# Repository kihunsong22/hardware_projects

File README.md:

View this project on [CADLAB.io](https://cadlab.io/project/1469). 

# hardware-projects
hardware designs and codes - some open-source, some from me

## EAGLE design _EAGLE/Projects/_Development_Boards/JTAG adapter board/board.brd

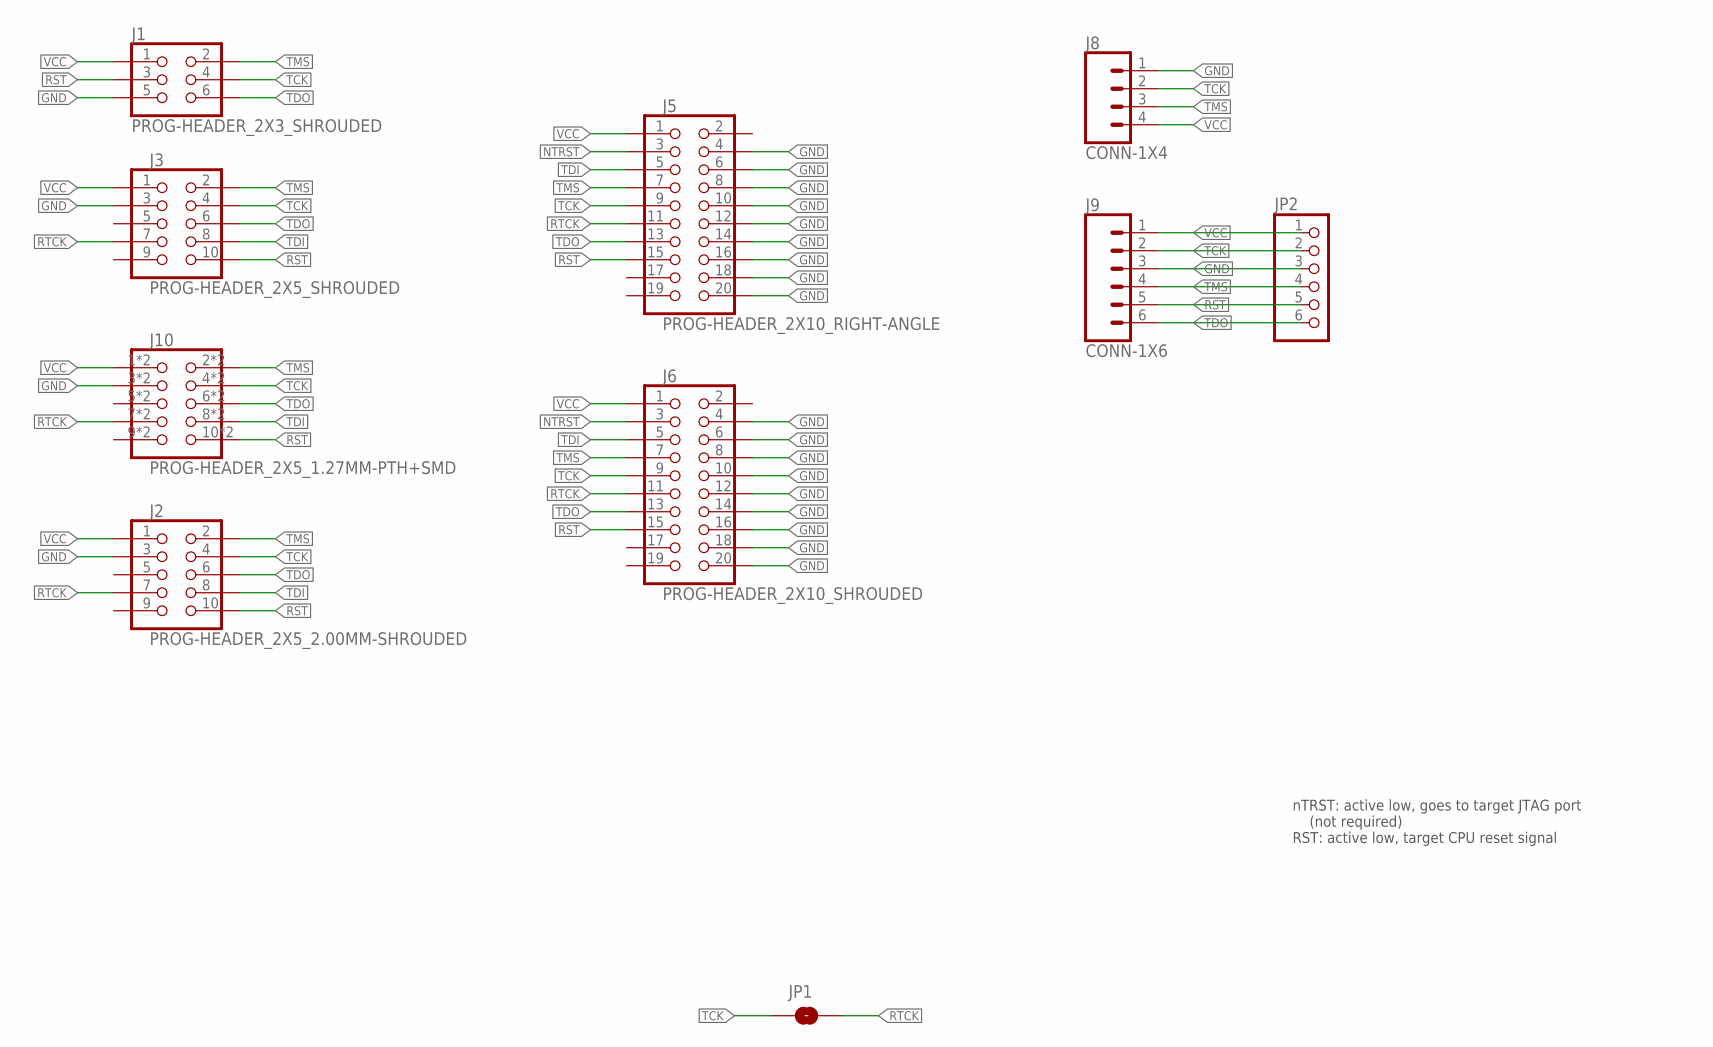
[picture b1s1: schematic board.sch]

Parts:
J1: PROG-HEADER_2X3_SHROUDED; 2X3-2.54MM-SHROUDED
J2: PROG-HEADER_2X5_2.00MM-SHROUDED; 2X5-2.00MM-SHROUDED
J3: PROG-HEADER_2X5_SHROUDED; 2X5-2.54MM-SHROUDED
J5: PROG-HEADER_2X10_RIGHT-ANGLE; 2X10-2.54MM-RIGHT-ANGLE
J6: PROG-HEADER_2X10_SHROUDED; 2X10-2.54MM-SHROUDED
J8: CONN-1X4; MOLEX-1X4-2.54MM
J9: CONN-1X6; MOLEX-1X6-2.54MM
J10: PROG-HEADER_2X5_1.27MM-PTH+SMD; 2X5-1.27MM_PTH+SMD
JP1: TCK-RTCK; SMT-JUMPER_2_NO_SILK
JP2: PINHD-1X6/OCT; 1X06/OCT

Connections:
2: J5.2, J6.2
GND: J1.5, J2.3, J3.3, J5.4, J5.6, J5.8, J5.10, J5.12, J5.14, J5.16, J5.18, J5.20, J6.4, J6.6, J6.8, J6.10, J6.12, J6.14, J6.16, J6.18, J6.20, J8.1, J9.3, J10.3, J10.13 (3), JP2.3
NTRST: J5.3, J6.3
RST: J1.3, J2.10, J3.10, J5.15, J6.15, J9.5, J10.10, J10.20 (10), JP2.5
RTCK: J2.7, J3.7, J5.11, J6.11, J10.7, J10.17 (7), JP1.2
TCK: J1.4, J2.4, J3.4, J5.9, J6.9, J8.2, J9.2, J10.4, J10.14 (4), JP1.1, JP2.2
TDI: J2.8, J3.8, J5.5, J6.5, J10.8, J10.18 (8)
TDO: J1.6, J2.6, J3.6, J5.13, J6.13, J9.6, J10.6, J10.16 (6), JP2.6
TMS: J1.2, J2.2, J3.2, J5.7, J6.7, J8.3, J9.4, J10.2, J10.12 (2), JP2.4
VCC: J1.1, J2.1, J3.1, J5.1, J6.1, J8.4, J9.1, J10.1, J10.11 (1), JP2.1

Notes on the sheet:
nTRST: active low, goes to target JTAG port (not required) RST: active low, target CPU reset signal

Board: 2 copper layers, 10 parts (1 on the bottom side), 10 nets, no tracks yet.

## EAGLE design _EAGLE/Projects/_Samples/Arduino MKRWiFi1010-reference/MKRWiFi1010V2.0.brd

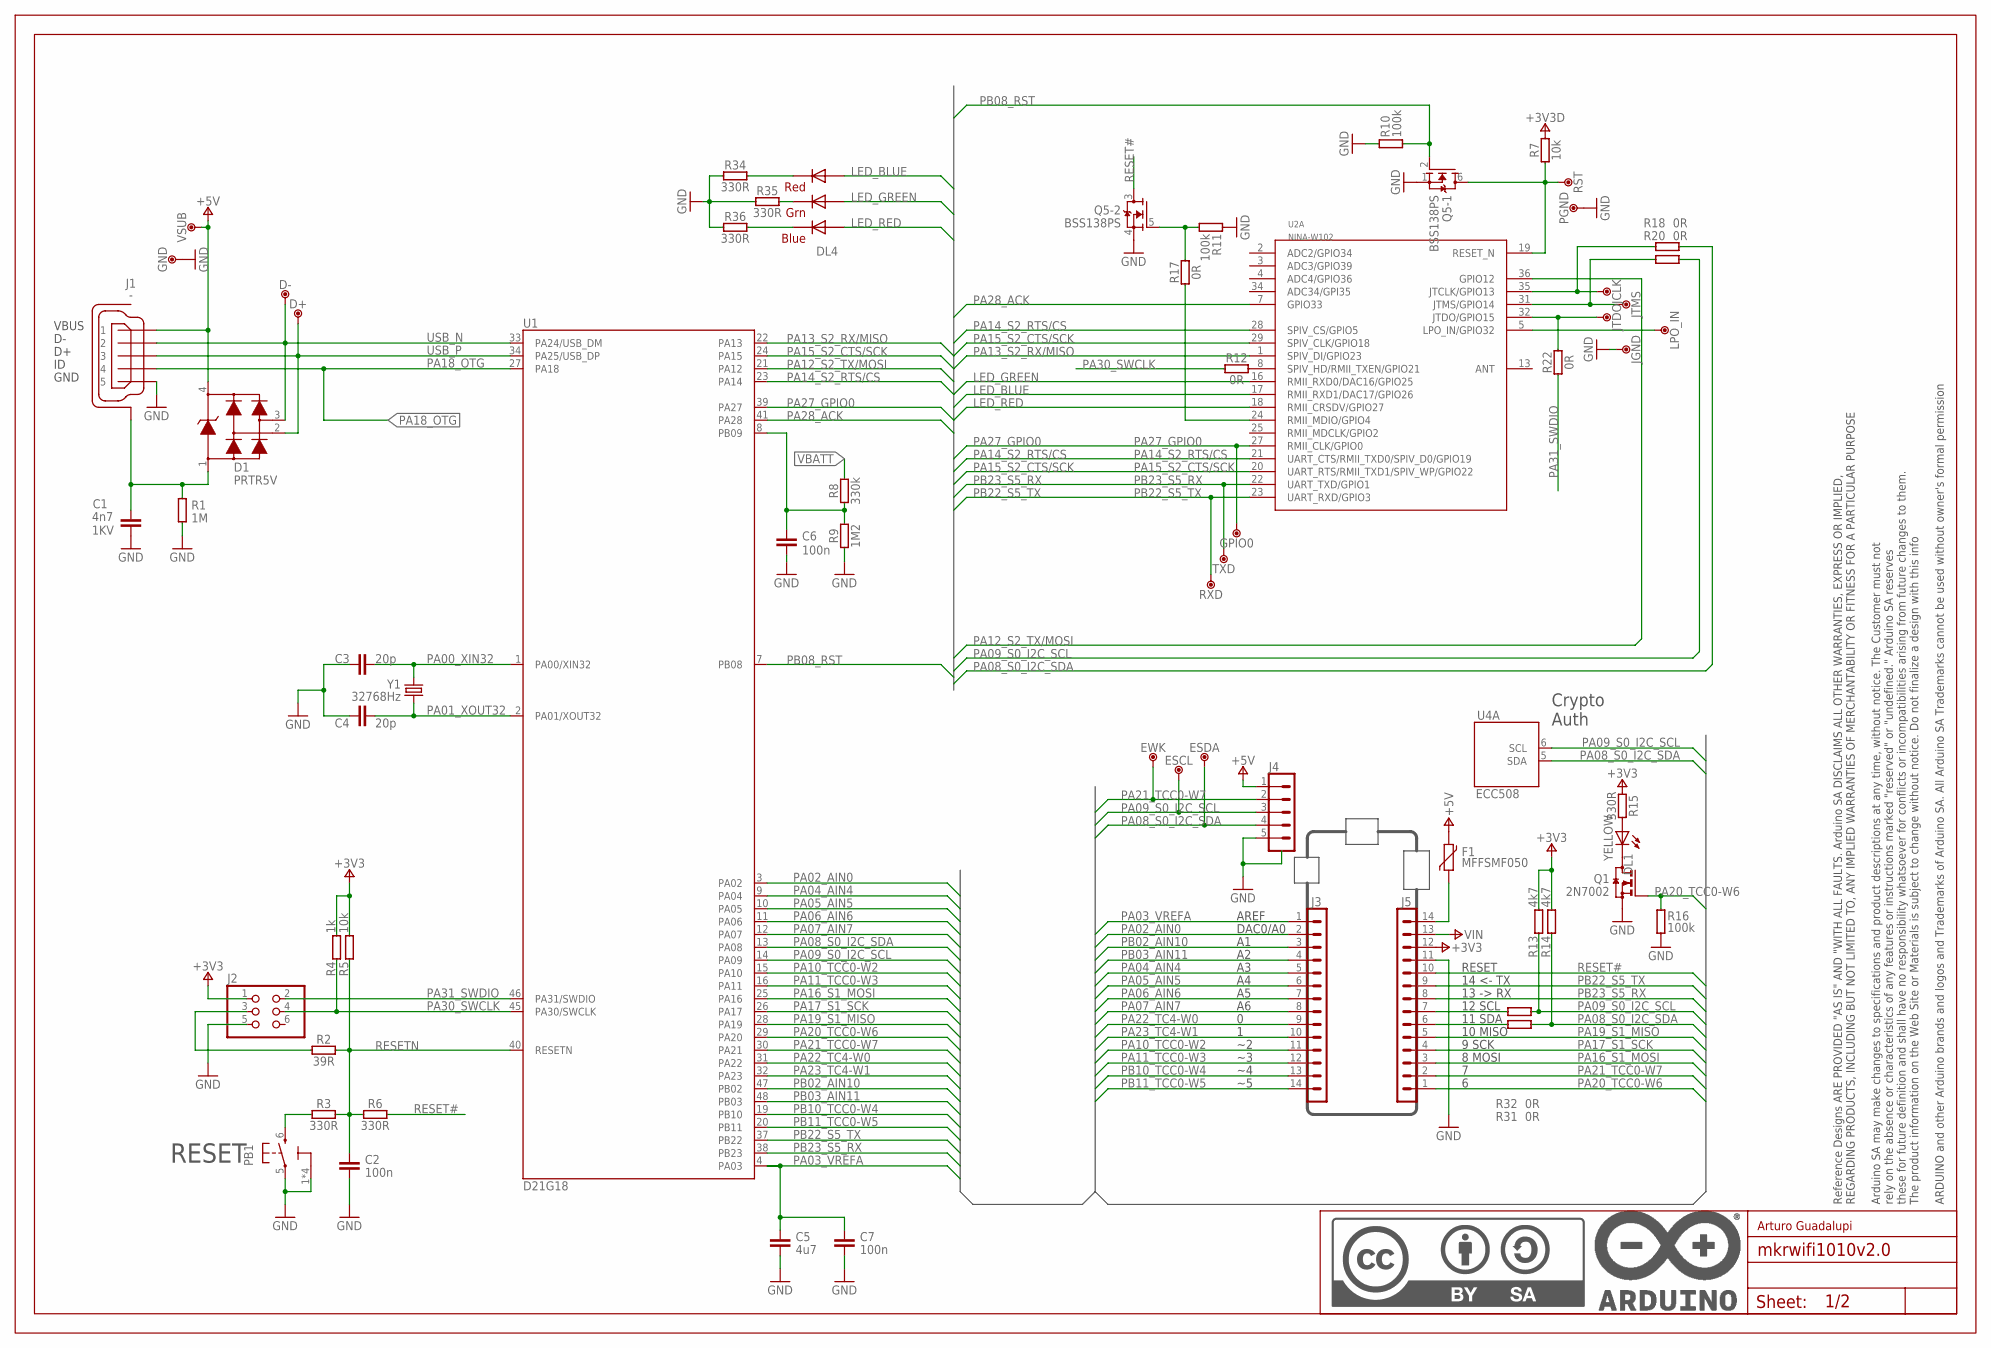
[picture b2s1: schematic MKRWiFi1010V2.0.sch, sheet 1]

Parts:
C1: 4n7; 0805-R2013X50N; VOLTAGE 1KV
C2, C6, C7: 100n; 0402-1005X55N
C3, C4: 20p; 0402-1005X55N
C5: 4u7; 0402-1005X55N
D1: PRTR5V; SOT190P230X110-4N
D+: DNP; TP-1.00MM
D-: DNP; TP-1.00MM
DL1: YELLOW; LEDC1608X80N-AK
DL4: RGB; RGBLED
ESCL: DNP; TP-1.00MM
ESDA: DNP; TP-1.00MM
EWK: DNP; TP-1.00MM
F1: MFFSMF050; 0603-1608X90N
FRAME1: DNP; FRAME
GND: DNP; TP-1.00MM
GPIO0: DNP; TP-0.8MM
J1: -; ZX62-AB-5PA
J2: DNP; 2X3_SMT
J3, J5: -; 1X14_SMD_TH
J4: -; SM05B-SRSS-TB
JCLK: DNP; TP-0.8MM
JGND: DNP; TP-0.8MM
JTDO: DNP; TP-0.8MM
JTMS: DNP; TP-0.8MM
LPO_IN: DNP; TP-1.27MM
PB1: PTS820; C&K_PTS820_NO_HOLES
PGND: DNP; TP-0.8MM
Q1: 2N7002; SOTFL50P160X78-3
Q5: BSS138PS; SOT363
R1: 1M; 0402-1005X55N
R2: 39R; 0402-1005X55N
R3, R6, R15, R34, R35, R36: 330R; 0402-1005X55N
R4: 1k; 0402-1005X55N
R5, R7: 10k; 0402-1005X55N
R8: 330k; 0402-1005X55N
R9: 1M2; 0402-1005X55N
R10, R11, R16: 100k; 0402-1005X55N
R12, R17, R18, R20, R22, R31, R32: 0R; 0402-1005X55N
R13, R14: 4k7; 0402-1005X55N
RST: DNP; TP-0.8MM
RXD: DNP; TP-0.8MM
TXD: DNP; TP-0.8MM
U1: D21G18; QFN50P700X700X90-49XN-EPSQ515
U2: NINA-W102; NINA-W1X
U4: ECC508; SON50P300X200X60-9N-EP160X140
VSUB: DNP; TP-1.00MM
Y1: 32768Hz; ABS07

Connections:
+3V3: J2.1, J5.12, R4.2, R5.2, R13.2, R14.2, R15.1; also elsewhere on the board
+3V3D: R7.2; also elsewhere on the board
+5V: D1.4, F1.2, J1.1, J4.1, VSUB.X; also elsewhere on the board
GND: C1.2, C2.2, C3.1, C4.1, C5.2, C6.2, C7.2, GND.X, J1.5, J2.5, J4.5, J4.SH1 (SH), J4.SH2 (SH), J5.11, JGND.X, PB1.1 (3), PB1.2 (3), PB1.3, PB1.4 (3), PB1.5 (1), PGND.X, Q1.S, Q5.1 (S), Q5.4 (S), R1.1, R9.1, R10.2, R11.2, R16.1, R34.1, R35.1, R36.1; also elsewhere on the board
LED_BLUE: DL4.2 (RED_A), U2.17 (RMII_RXD1/DAC17/GPIO26)
LED_GREEN: DL4.1 (GREEN_A), U2.16 (RMII_RXD0/DAC16/GPIO25)
LED_RED: DL4.3 (BLUE_A), U2.18 (RMII_CRSDV/GPIO27)
N17658775: PB1.6 (2), R3.1
unnamed: C1.1, D1.1, J1.6 (SH), J1.7 (SH), J1.8 (SH), J1.9 (SH), J1.10 (SH), J1.11 (SH), R1.2
unnamed: F1.1, J5.14
unnamed: J2.3, R2.1
unnamed: J5.7, R32.1
unnamed: C6.1, R8.1, R9.2, U1.8 (PB09)
unnamed: DL1.A, R15.2
unnamed: J5.6, R31.1
unnamed: Q5.6 (D), R7.1, RST.X, U2.19 (RESET_N)
unnamed: DL1.C, Q1.D
unnamed: JCLK.X, R18.1, U2.35 (JTCLK/GPIO13)
unnamed: JTMS.X, R20.1, U2.31 (JTMS/GPIO14)
unnamed: R17.1, U2.24 (RMII_MDIO/GPIO4)
unnamed: DL4.5 (RED_C), R34.2
unnamed: DL4.6 (GREEN_C), R35.2
unnamed: DL4.4 (BLUE_C), R36.2
unnamed: LPO_IN.X, U2.5 (LPO_IN/GPIO32)
unnamed: JTDO.X, R22.2, U2.32 (JTDO/GPIO15)
unnamed: R12.2, U2.8 (SPIV_HD/RMII_TXEN/GPIO21)
unnamed: Q5.5 (G), R11.1, R17.2
PA00_XIN32: C3.2, U1.1 (PA00/XIN32), Y1.2
PA01_XOUT32: C4.2, U1.2 (PA01/XOUT32), Y1.1
PA02_AIN0: J3.2, U1.3 (PA02)
PA03_VREFA: C5.1, C7.1, J3.1, U1.4 (PA03)
PA04_AIN4: J3.5, U1.9 (PA04)
PA05_AIN5: J3.6, U1.10 (PA05)
PA06_AIN6: J3.7, U1.11 (PA06)
PA07_AIN7: J3.8, U1.12 (PA07)
PA08_S0_I2C_SDA: ESDA.X, J4.4, R14.1, R18.2, R31.2, U1.13 (PA08), U4.5 (SDA); also elsewhere on the board
PA09_S0_I2C_SCL: ESCL.X, J4.3, R13.1, R20.2, R32.2, U1.14 (PA09), U4.6 (SCL); also elsewhere on the board
PA10_TCC0-W2: J3.11, U1.15 (PA10)
PA11_TCC0-W3: J3.12, U1.16 (PA11)
PA12_S2_TX/MOSI: U1.21 (PA12), U2.36 (GPIO12)
PA13_S2_RX/MISO: U1.22 (PA13), U2.1 (SPIV_DI/GPIO23)
PA14_S2_RTS/CS: U1.23 (PA14), U2.21 (UART_CTS/RMII_TXD0/SPIV_D0/GPIO19), U2.28 (SPIV_CS/GPIO5)
PA15_S2_CTS/SCK: U1.24 (PA15), U2.20 (UART_RTS/RMII_TXD1/SPIV_WP/GPIO22), U2.29 (SPIV_CLK/GPIO18)
PA16_S1_MOSI: J5.3, U1.25 (PA16)
PA17_S1_SCK: J5.4, U1.26 (PA17)
PA18_OTG: J1.4, U1.27 (PA18); also elsewhere on the board
PA19_S1_MISO: J5.5, U1.28 (PA19)
PA20_TCC0-W6: J5.1, Q1.G, R16.2, U1.29 (PA20)
PA21_TCC0-W7: EWK.X, J4.2, J5.2, U1.30 (PA21)
PA22_TC4-W0: J3.9, U1.31 (PA22)
PA23_TC4-W1: J3.10, U1.32 (PA23)
PA27_GPIO0: GPIO0.X, U1.39 (PA27), U2.27 (RMII_CLK/GPIO0)
PA28_ACK: U1.41 (PA28), U2.7 (GPIO33)
PA30_SWCLK: J2.4, R4.1, R12.1, U1.45 (PA30/SWCLK)
PA31_SWDIO: J2.2, R22.1, U1.46 (PA31/SWDIO)
PB02_AIN10: J3.3, U1.47 (PB02)
PB03_AIN11: J3.4, U1.48 (PB03)
PB08_RST: Q5.2 (G), R10.1, U1.7 (PB08)
PB10_TCC0-W4: J3.13, U1.19 (PB10)
PB11_TCC0-W5: J3.14, U1.20 (PB11)
PB22_S5_TX: J5.9, RXD.X, U1.37 (PB22), U2.23 (UART_RXD/GPIO3)
PB23_S5_RX: J5.8, TXD.X, U1.38 (PB23), U2.22 (UART_TXD/GPIO1)
RESET#: J5.10, Q5.3 (D), R6.2
RESETN: C2.1, R2.2, R3.2, R5.1, R6.1, U1.40 (RESETN)
USB_N: D1.3, D-.X, J1.2, U1.33 (PA24/USB_DM)
USB_P: D1.2, D+.X, J1.3, U1.34 (PA25/USB_DP)
VBATT: R8.2; also elsewhere on the board
VIN: J5.13; also elsewhere on the board

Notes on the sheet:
14 <- TX
13 -> RX
12 SCL
RESET
11 SDA
8 MOSI
9 SCK
10 MISO
AREF
DAC0/A0
Crypto Auth
Arturo Guadalupi

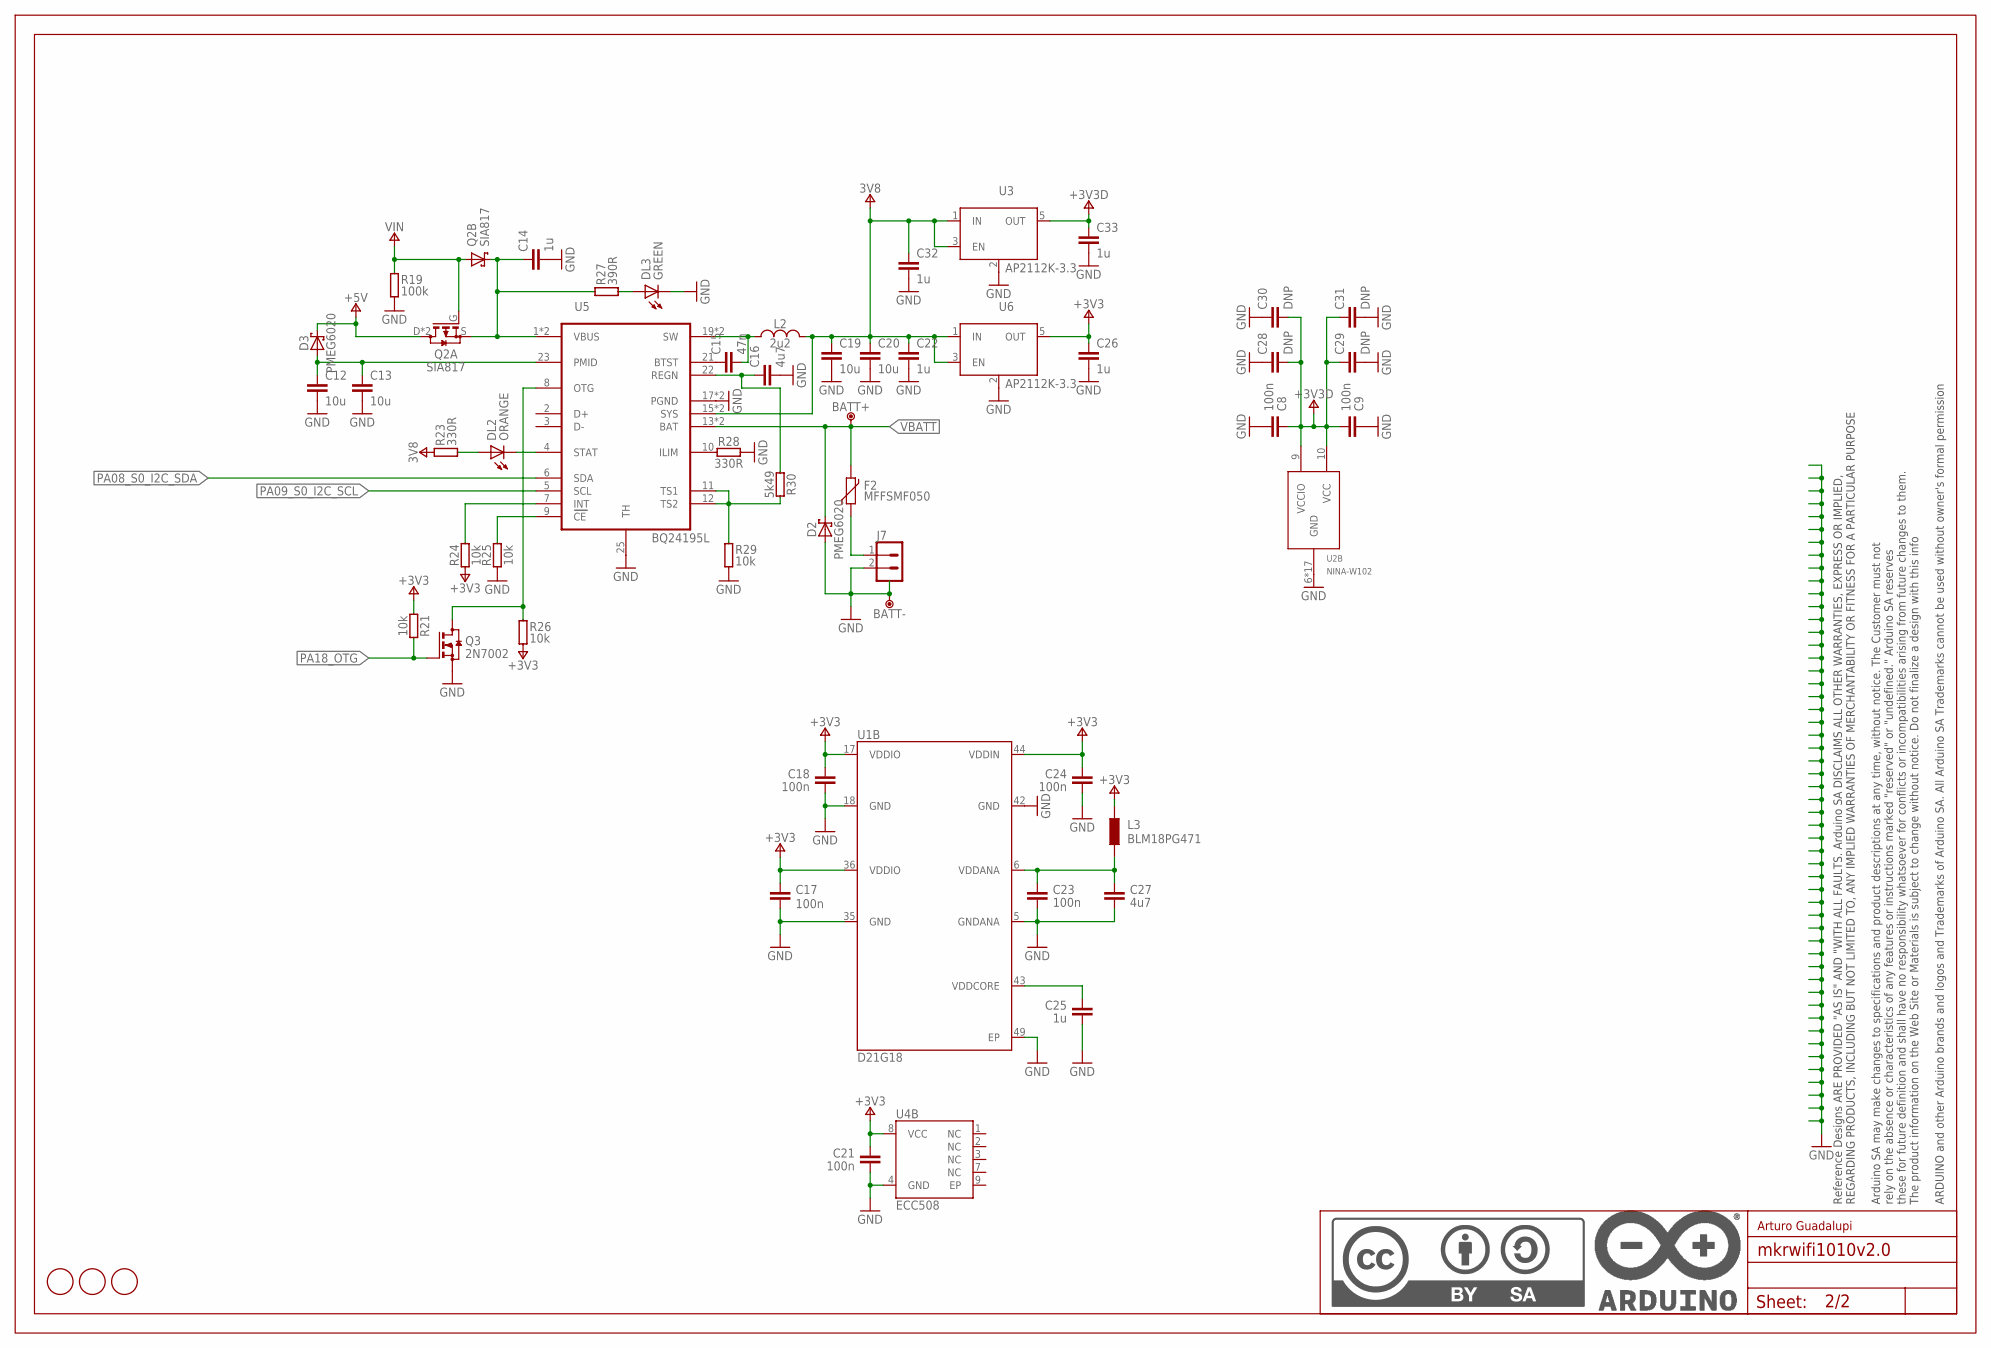
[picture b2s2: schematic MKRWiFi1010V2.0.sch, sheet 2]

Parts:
BATT+: DNP; TP-1.00MM
BATT-: DNP; TP-1.00MM
C8, C9, C17, C18, C21, C23, C24: 100n; 0402-1005X55N
C12, C13, C19, C20: 10u; 0603-1608X90N
C14, C22, C25, C26, C32, C33: 1u; 0402-1005X55N
C15: 47n; 0402-1005X55N
C16: 4u7; 0402-1005X55N
C27: 4u7; 0603-1608X90N
C28, C29: DNP; 0402-1005X55N
C30, C31: DNP; 0603-1608X90N
D2, D3: PMEG6020; SODFL3517X110N
DL2: ORANGE; LEDC1608X80N-AK
DL3: GREEN; LEDC1608X80N-AK
F2: MFFSMF050; 0603-1608X90N
FD1, FD2, FD3: DNP; FD-1-1.5
FRAME2: DNP; FRAME
J7: -; JST-S2B-PH-SM4-TB
L2: 2u2; SRP4020
L3: BLM18PG471; 0603-1608X90N
Q2: SIA817; SON65P205X205X75-8N-MWSD
Q3: 2N7002; SOTFL50P160X78-3
R19: 100k; 0402-1005X55N
R21, R24, R25, R26, R29: 10k; 0402-1005X55N
R23, R28: 330R; 0402-1005X55N
R27: 390R; 0402-1005X55N
R30: 5k49; 0402-1005X55N
U1: D21G18; QFN50P700X700X90-49XN-EPSQ515
U2: NINA-W102; NINA-W1X
U3, U6: AP2112K-3.3; SOT25
U4: ECC508; SON50P300X200X60-9N-EP160X140
U5: BQ24195L; QFN24

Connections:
+3V3: C17.1, C18.1, C21.1, C24.1, C26.1, L3.1, R21.1, R24.1, R26.1, U1.17 (VDDIO), U1.36 (VDDIO), U1.44 (VDDIN), U4.8 (VCC), U6.5 (OUT); also elsewhere on the board
+3V3D: C8.1, C9.2, C28.2, C29.1, C30.2, C31.1, C33.1, U2.9 (VCCIO), U2.10 (VCC), U3.5 (OUT); also elsewhere on the board
+3V8: C19.1, C20.1, C22.1, C32.1, L2.2, R23.2, U3.1 (IN), U3.3 (EN), U5.15 (SYS), U5.16 (SYS), U6.1 (IN), U6.3 (EN)
+5V: D3.C, Q2.D, Q2.D2 (D); also elsewhere on the board
GND: BATT-.X, C8.2, C9.1, C12.2, C13.2, C14.2, C16.2, C17.2, C18.2, C19.2, C20.2, C21.2, C22.2, C23.2, C24.2, C25.2, C26.2, C27.2, C28.1, C29.2, C30.1, C31.2, C32.2, C33.2, D2.A, DL3.C, J7.2, J7.3 (SH), J7.4 (SH), Q3.S, R19.1, R25.1, R28.2, R29.1, U1.5 (GNDANA), U1.18 (GND), U1.35 (GND), U1.42 (GND), U1.49 (EP), U2.6 (GND), U2.12 (GND), U2.14 (GND), U2.26 (GND), U2.30 (GND), U2.GND@1 (GND), U2.GND@2 (GND), U2.GND@3 (GND), U2.GND@4 (GND), U2.GND@5 (GND), U2.GND@6 (GND), U2.GND@7 (GND), U2.GND@8 (GND), U2.GND@9 (GND), U2.GND@10 (GND), U2.GND@11 (GND), U2.GND@12 (GND), U3.2 (GND/ADJ), U4.4 (GND), U5.17 (PGND), U5.18 (PGND), U5.25 (TH), U6.2 (GND/ADJ); also elsewhere on the board
N17798864: DL2.A, R23.1
N17834267: DL3.A, R27.1
N17852357: C23.1, C27.1, L3.2, U1.6 (VDDANA)
N17852431: C25.1, U1.43 (VDDCORE)
unnamed: F2.1, J7.1
unnamed: C15.2, L2.1, U5.19 (SW), U5.20 (SW)
unnamed: C14.1, Q2.K (C), Q2.K2 (C), Q2.S, R27.2, U5.1 (VBUS), U5.24 (VBUS)
unnamed: C15.1, U5.21 (BTST)
unnamed: R28.1, U5.10 (ILIM)
unnamed: C16.1, R30.1, U5.22 (REGN)
unnamed: Q3.D, R26.2, U5.8 (OTG)
unnamed: R29.2, R30.2, U5.11 (TS1), U5.12 (TS2)
unnamed: R25.2, U5.9 (CE)
PA08_S0_I2C_SDA: U5.6 (SDA); also elsewhere on the board
PA09_S0_I2C_SCL: U5.5 (SCL); also elsewhere on the board
PA18_OTG: Q3.G, R21.2; also elsewhere on the board
PMICINT: R24.2, U5.7 (INT)
STAT: DL2.C, U5.4 (STAT)
VBATT: BATT+.X, D2.C, F2.2, U5.13 (BAT), U5.14 (BAT); also elsewhere on the board
VIN: Q2.A, Q2.G, R19.2; also elsewhere on the board
VUSB1: C12.1, C13.1, D3.A, U5.23 (PMID)

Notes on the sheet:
Arturo Guadalupi

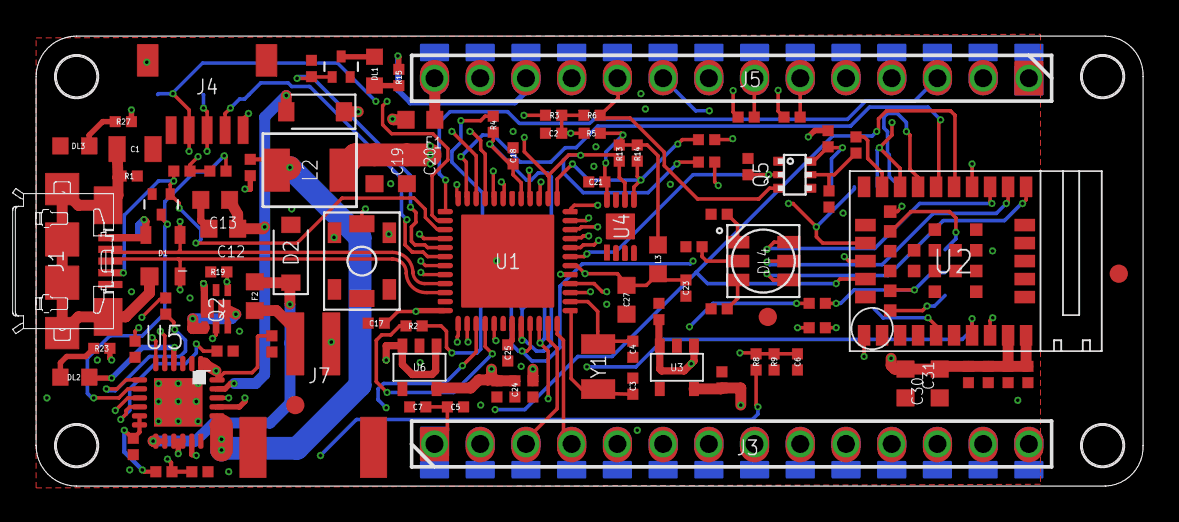
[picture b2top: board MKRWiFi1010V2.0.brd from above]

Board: 4 copper layers, 61.5 x 25.0 mm, 123 parts (1 on the bottom side), 85 nets.

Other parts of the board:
U$5, U$6, U$7, U$8: MH_RND_F_2.2MM_NM

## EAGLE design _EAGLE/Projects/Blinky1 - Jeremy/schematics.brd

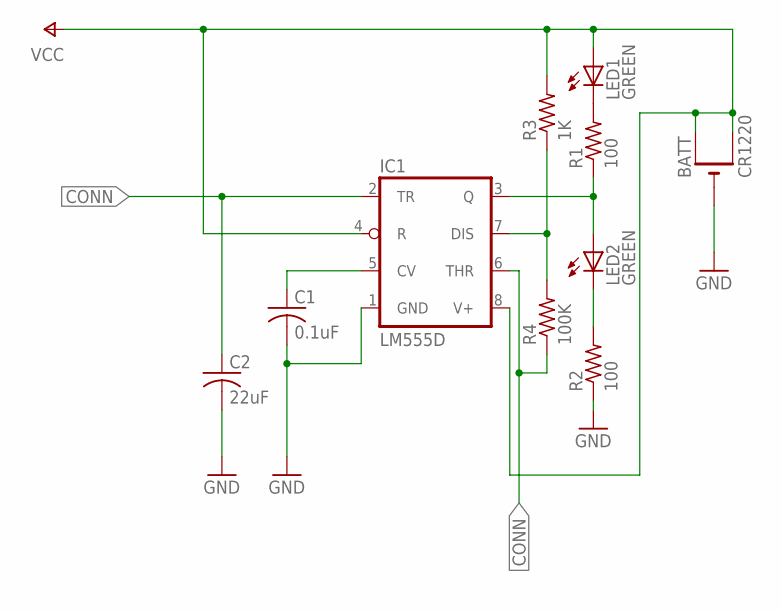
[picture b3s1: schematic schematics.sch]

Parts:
BATT: CR1220; CR1220-SMD
C1: 0.1uF; C0805
C2: 22uF; C0805
IC1: LM555D; SO08
LED1, LED2: GREEN; CHIPLED_0805
R1, R2: 100; R0805
R3: 1K; R0805
R4: 100K; R0805

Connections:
CONN: C2.1, IC1.2 (TR), IC1.6 (THR), R4.1
GND: BATT.-, C1.2, C2.2, IC1.1 (GND), R2.1
unnamed: IC1.3 (Q), LED2.A, R1.1
unnamed: LED1.C, R1.2
unnamed: LED2.C, R2.2
unnamed: IC1.7 (DIS), R3.1, R4.2
unnamed: C1.1, IC1.5 (CV)
V+: BATT.+$1 (+), BATT.+$2 (+1), IC1.4 (R), IC1.8 (V+), LED1.A, R3.2

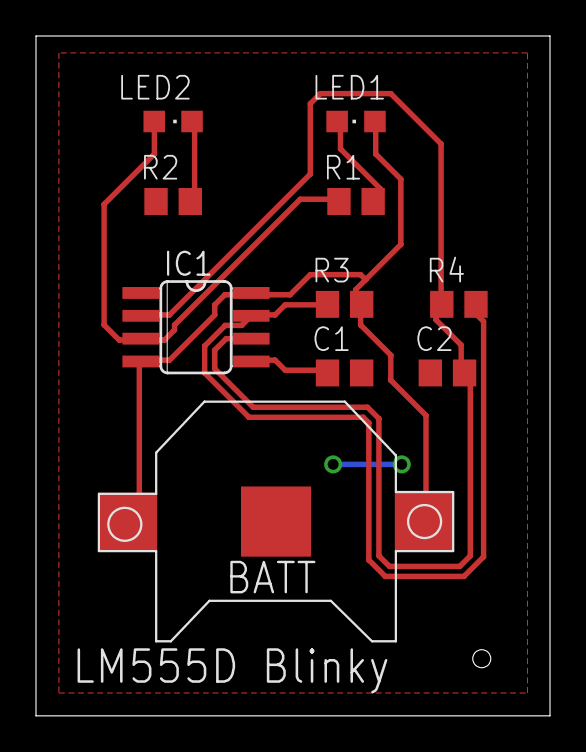
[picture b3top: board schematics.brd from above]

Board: 2 copper layers, 28.6 x 37.8 mm, 10 parts (0 on the bottom side), 8 nets.

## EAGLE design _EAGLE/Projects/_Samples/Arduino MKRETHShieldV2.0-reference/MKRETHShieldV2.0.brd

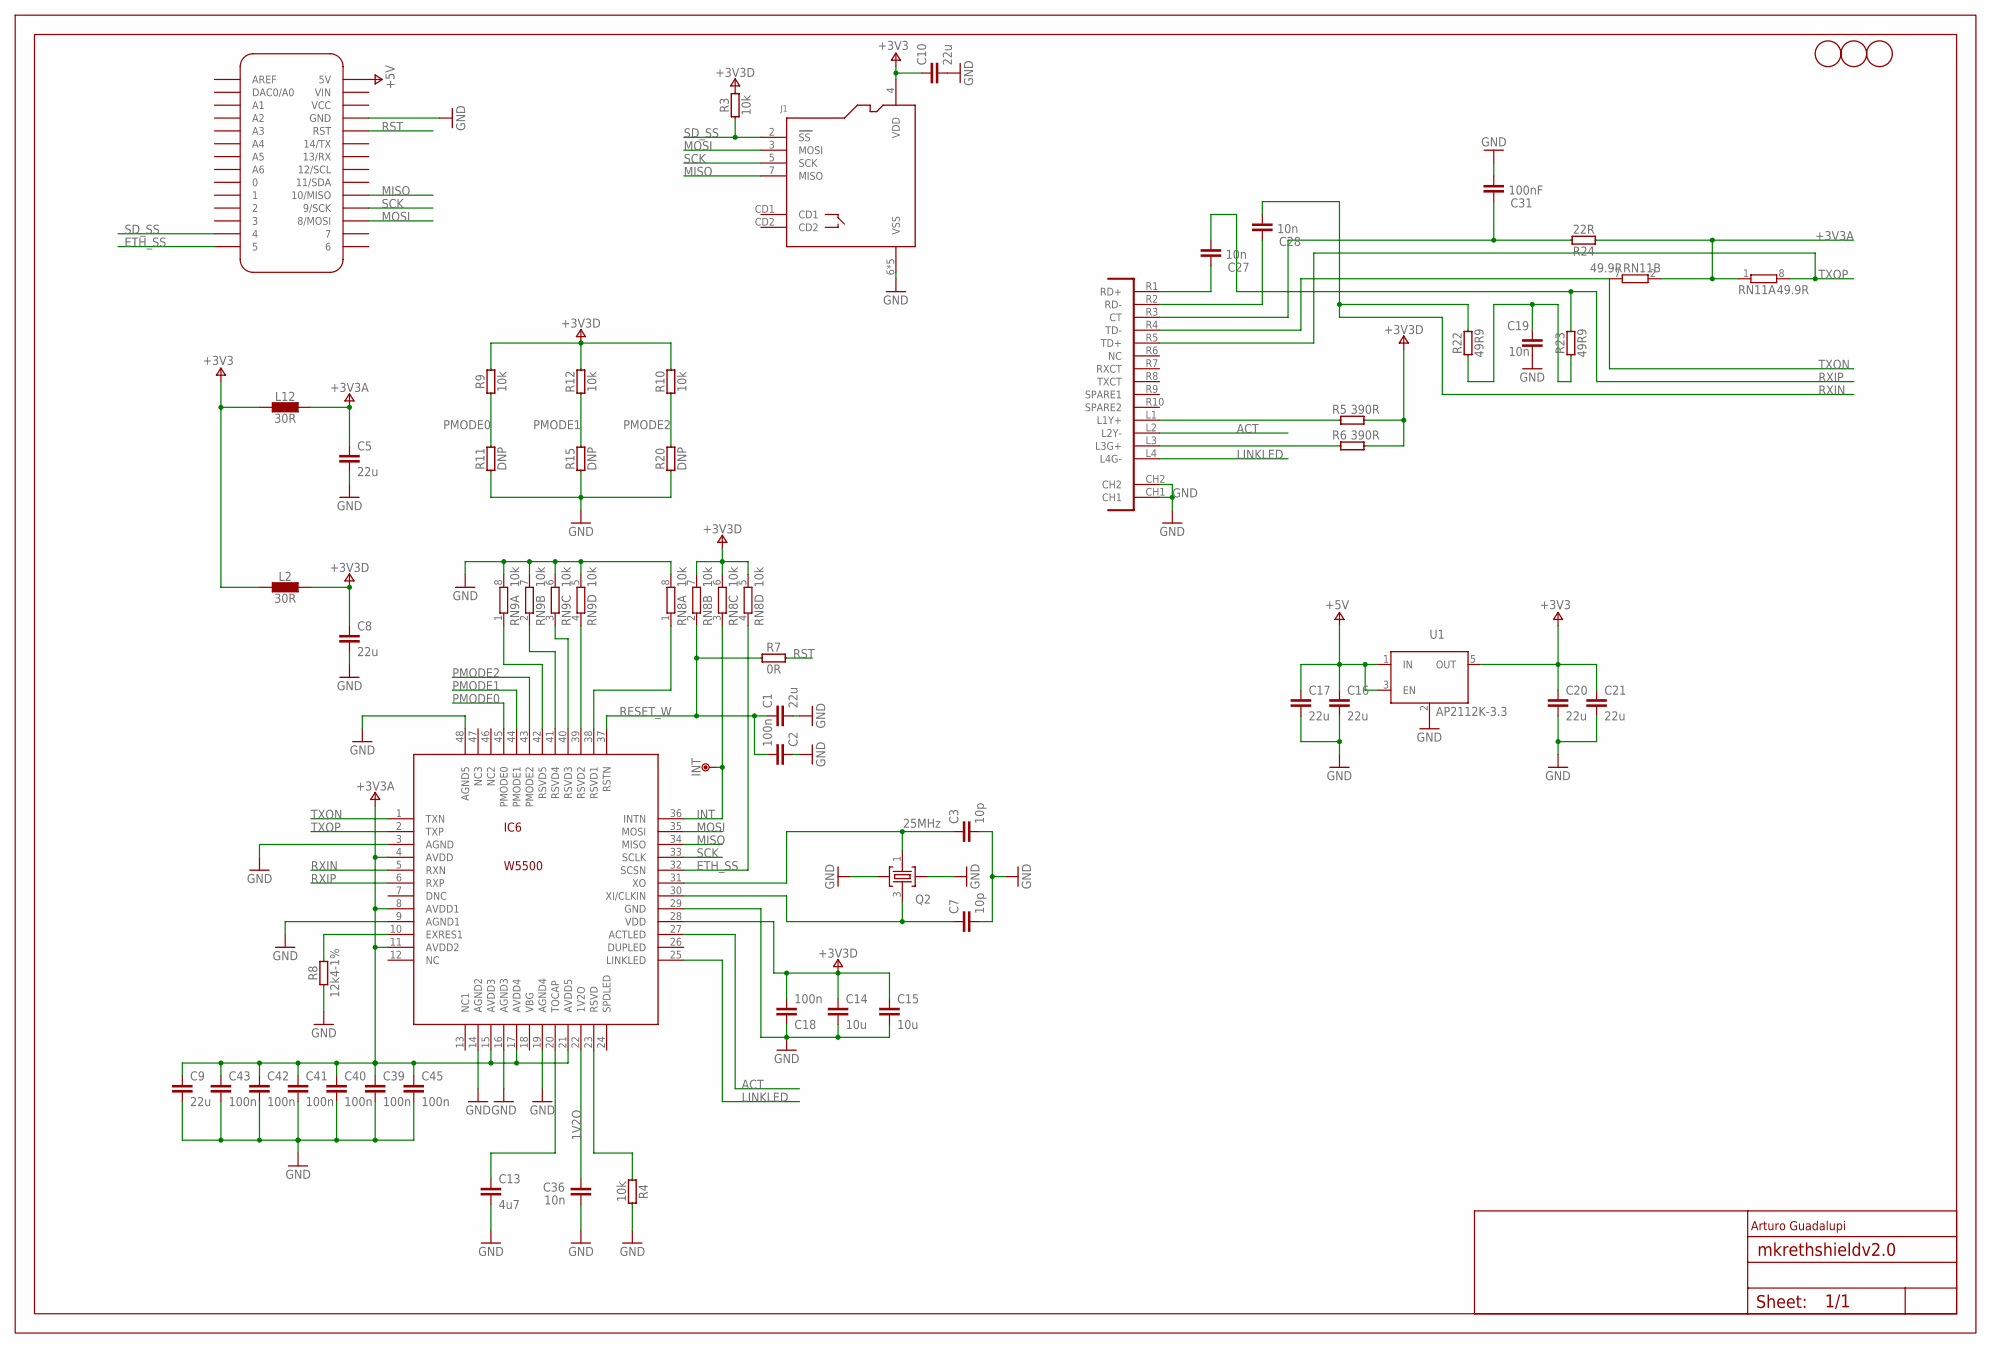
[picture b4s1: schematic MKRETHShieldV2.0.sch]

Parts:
C1, C5, C8, C9, C10, C16, C17, C20, C21: 22u; 0805-R2013X50N
C2, C18, C39, C40, C41, C42, C43, C45: 100n; 0402-1005X55N
C3, C7: 10p; 0402-1005X55N
C13: 4u7; 0603-1608X90N
C14, C15: 10u; 0603-1608X90N
C19, C27, C28, C36: 10n; 0402-1005X55N
C31: 100nF; 0402-1005X55N
FRAME1: DNP; FRAME
IC6: W5500; TQFP48-7X7
INT: DNP; TP-1.27MM
J1: -; AMPHENOL_114-00841-68
L2, L12: 30R; 0805-R2013X50N
MKR1: DNP; MKRBOARD-DIM
Q2: 25MHz; CRYSTAL3.2X2.5
R3, R4, R9, R10, R12: 10k; 0402-1005X55N
R5, R6: 390R; 0402-1005X55N
R7: 0R; 0402-1005X55N
R8: 12k4-1%; 0402-1005X55N
R11, R15, R20: DNP; 0402-1005X55N
R22, R23: 49R9; 0402-1005X55N
R24: 22R; 0402-1005X55N
RN8, RN9: 10k; CAY16
RN11: 49.9R; CAY16
U1: AP2112K-3.3; SOT25
U$1, U$2, U$3: DNP; FD-1-1.5
UC1: -; POE-RJ45

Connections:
1V2O: C36.2, IC6.22 (1V2O)
+3V3: C10.1, C20.1, C21.1, J1.4 (VDD), L2.1, L12.1, U1.5 (OUT)
+3V3A: C5.1, C9.1, C39.1, C40.1, C41.1, C42.1, C43.1, C45.1, IC6.4 (AVDD), IC6.8 (AVDD1), IC6.11 (AVDD2), IC6.15 (AVDD3), IC6.17 (AVDD4), IC6.21 (AVDD5), L12.2, R24.1, RN11.1, RN11.2 (1)
+3V3D: C8.1, C14.1, C15.1, C18.2, IC6.28 (VDD), L2.2, R3.2, R5.2, R6.2, R9.2, R10.2, R12.2, RN8.5 (2), RN8.6 (2), RN8.7 (2)
+5V: C16.1, C17.1, MKR1.5V, U1.1 (IN), U1.3 (EN)
ACT: IC6.27 (ACTLED), UC1.L2 (L2Y-)
DUPLED: IC6.26 (DUPLED)
ETH_SS: IC6.32 (SCSN), MKR1.5, RN8.4 (1)
GND: C1.2, C2.1, C3.2, C5.2, C7.2, C8.2, C9.2, C10.2, C13.2, C14.2, C15.2, C16.2, C17.2, C18.1, C19.1, C20.2, C21.2, C31.1, C36.1, C39.2, C40.2, C41.2, C42.2, C43.2, C45.2, IC6.3 (AGND), IC6.9 (AGND1), IC6.14 (AGND2), IC6.16 (AGND3), IC6.19 (AGND4), IC6.29 (GND), IC6.48 (AGND5), J1.6 (VSS), J1.SH1 (VSS), J1.SH2 (VSS), J1.SH3 (VSS), J1.SH4 (VSS), MKR1.GND, Q2.2, Q2.4, R4.1, R8.1, R11.1, R15.1, R20.1, RN8.8 (2), RN9.5 (2), RN9.6 (2), RN9.7 (2), RN9.8 (2), U1.2 (GND/ADJ), UC1.CH1, UC1.CH2
INT: IC6.36 (INTN), INT.X, RN8.3 (1)
LINKLED: IC6.25 (LINKLED), UC1.L4 (L4G-)
MISO: IC6.34 (MISO), J1.7 (MISO), MKR1.10 (10/MISO)
MOSI: IC6.35 (MOSI), J1.3 (MOSI), MKR1.8 (8/MOSI)
unnamed: C3.1, IC6.31 (XO), Q2.1
unnamed: IC6.39 (RSVD2), RN9.4 (1)
unnamed: R6.1, UC1.L3 (L3G+)
unnamed: IC6.23 (RSVD), R4.2
unnamed: R5.1, UC1.L1 (L1Y+)
unnamed: C19.2, R22.1, R23.1
unnamed: C27.2, UC1.R1 (RD+)
unnamed: C28.2, UC1.R2 (RD-)
unnamed: IC6.40 (RSVD3), RN9.3 (1)
unnamed: IC6.41 (RSVD4), RN9.2 (1)
unnamed: C31.2, R24.2, UC1.R3 (CT)
unnamed: IC6.42 (RSVD5), RN9.1
unnamed: C13.1, IC6.20 (TOCAP)
unnamed: IC6.38 (RSVD1), RN8.1
unnamed: IC6.10 (EXRES1), R8.2
NC: IC6.12 (NC)
OSC2E2: C7.1, IC6.30 (XI/CLKIN), Q2.3
PMODE0: IC6.45 (PMODE0), R9.1, R11.2
PMODE1: IC6.44 (PMODE1), R12.1, R15.2
PMODE2: IC6.43 (PMODE2), R10.1, R20.2
RESET_W: C1.1, C2.2, IC6.37 (RSTN), R7.1, RN8.2 (1)
RST: MKR1.RST, R7.2
RXIN: C28.1, IC6.5 (RXN), R22.2
RXIP: C27.1, IC6.6 (RXP), R23.2
SCK: IC6.33 (SCLK), J1.5 (SCK), MKR1.9 (9/SCK)
SD_SS: J1.2 (SS), MKR1.4, R3.1
TXON: IC6.1 (TXN), RN11.7 (2), UC1.R4 (TD-)
TXOP: IC6.2 (TXP), RN11.8 (2), UC1.R5 (TD+)

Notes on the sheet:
Arturo Guadalupi

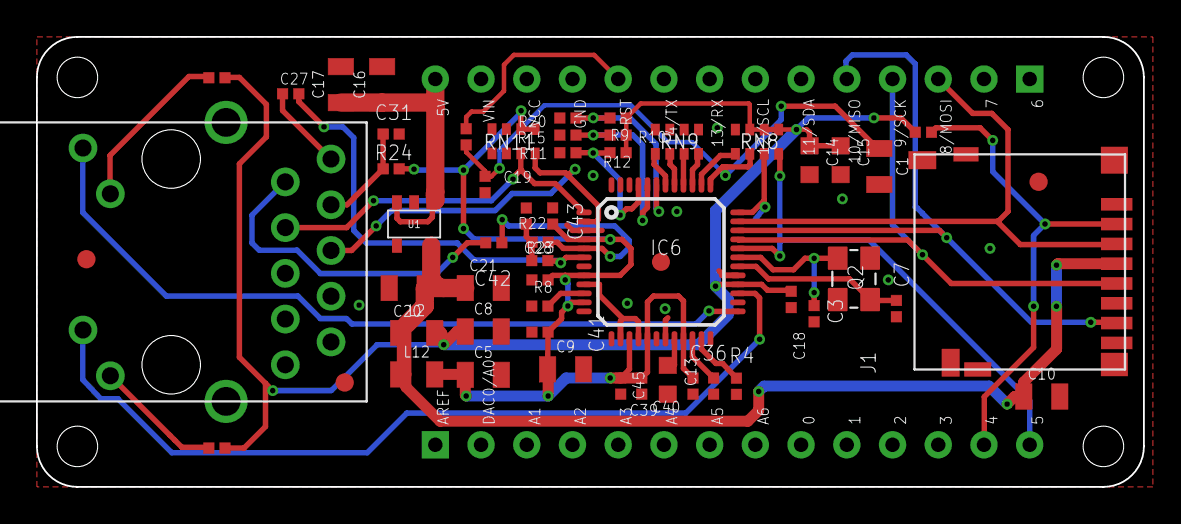
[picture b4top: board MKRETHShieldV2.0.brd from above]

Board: 2 copper layers, 61.5 x 25.0 mm, 58 parts (0 on the bottom side), 39 nets.

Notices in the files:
_EAGLE/Projects/_Samples/Arduino MKRETHShieldV2.0-reference/MKRETHShieldV2.0.brd:
Copyright (c) 2016-2017 Arduino LLC.  All right reserved. EAGLE Design Rules
parts and their libraries:
SparkFun-Connectors: Licensing: Creative Commons ShareAlike 4.0 International - https://creativecommons.org/licenses/by-sa/4.0
diy-modules: Released under the Creative Commons Attribution 4.0 International License: http://creativecommons.org/licenses/by/4.0
